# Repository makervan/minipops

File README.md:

# MiniPops
PCB design for Jan Ostman's O2 synth. Based around the Arduino Pro Mini board.

## License
Hardware designs created by Severin Schols, and shared under CC-BY-SA-4.0. See LICENSE for more information.

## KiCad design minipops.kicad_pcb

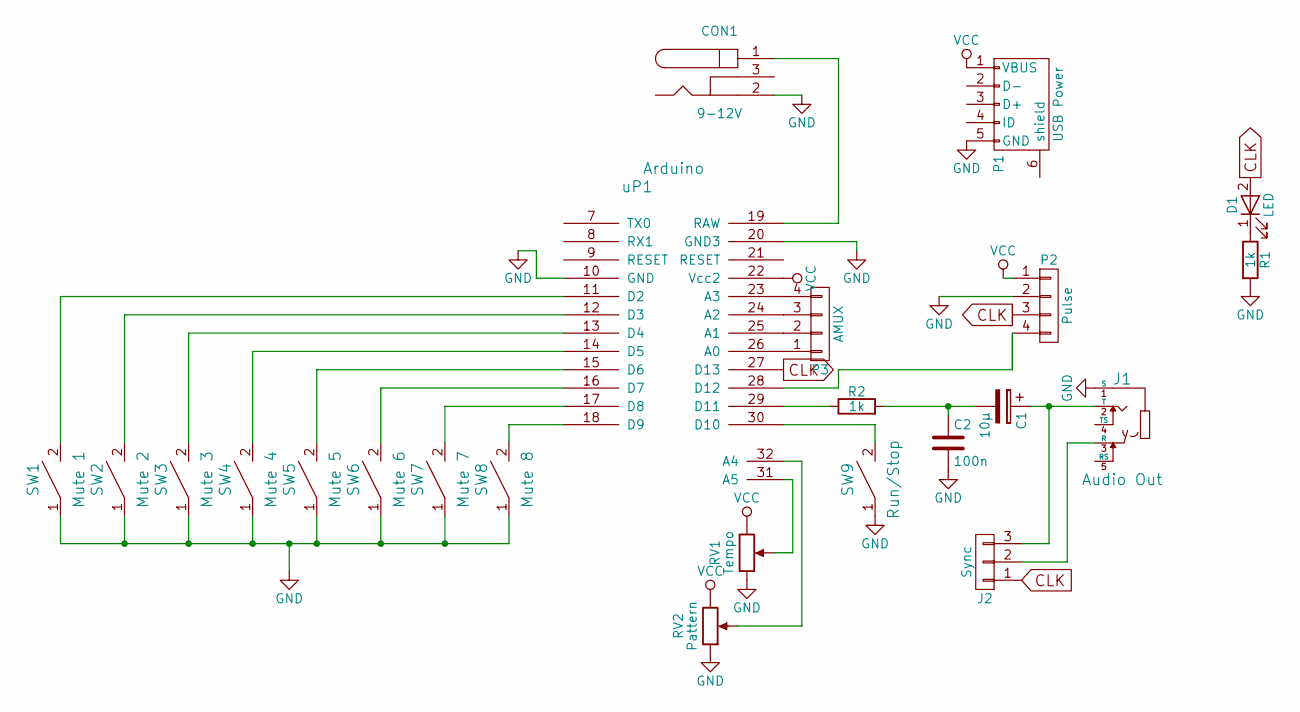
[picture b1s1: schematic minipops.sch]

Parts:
C1: 10µ; C_Radial_D5_L6_P2.5
C2: 100n; C_Rect_L4_W2.5_P2.5
CON1: 9-12V; BARREL_JACK
D1: LED; LED-5MM
J1: Audio Out; AudioJack3.5mm
J2: Sync; Pin_Header_Straight_1x03
P1: USB Power; USB_Micro-B
P2: Pulse; Pin_Header_Straight_1x04
P3: AMUX; Pin_Header_Straight_1x04
R1, R2: 1k; Resistor_Horizontal_RM10mm
RV1: Tempo; Potentiometer_Alpha-RV09
RV2: Pattern; Potentiometer_Alpha-RV09
SW1: Mute 1; Pin_Header_Straight_1x03
SW2: Mute 2; Pin_Header_Straight_1x03
SW3: Mute 3; Pin_Header_Straight_1x03
SW4: Mute 4; Pin_Header_Straight_1x03
SW5: Mute 5; Pin_Header_Straight_1x03
SW6: Mute 6; Pin_Header_Straight_1x03
SW7: Mute 7; Pin_Header_Straight_1x03
SW8: Mute 8; Pin_Header_Straight_1x03
SW9: Run/Stop; Pin_Header_Straight_1x03
uP1: Arduino; ArduProMini-6

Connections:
CLK: D1.2 (A), J2.1, P2.3, uP1.27 (D13)
GND: C2.2, CON1.2, J1.1 (S), P1.5 (GND), P2.2, R1.2, RV1.1, RV2.1, SW1.1, SW2.1, SW3.1, SW4.1, SW5.1, SW6.1, SW7.1, SW8.1, SW9.1, uP1.10 (GND), uP1.20 (GND3)
unnamed: C1.1, J1.2 (T), J2.3
unnamed: C1.2, C2.1, R2.2
unnamed: CON1.1, uP1.19 (RAW)
unnamed: D1.1 (K), R1.1
unnamed: J1.3 (R), J2.2
unnamed: P2.4, uP1.28 (D12)
unnamed: P3.1, uP1.26 (A0)
unnamed: P3.2, uP1.25 (A1)
unnamed: P3.3, uP1.24 (A2)
unnamed: P3.4, uP1.23 (A3)
unnamed: R2.1, uP1.29 (D11)
unnamed: RV1.2, uP1.31 (A5)
unnamed: RV2.2, uP1.32 (A4)
unnamed: SW1.2, uP1.11 (D2)
unnamed: SW2.2, uP1.12 (D3)
unnamed: SW3.2, uP1.13 (D4)
unnamed: SW4.2, uP1.14 (D5)
unnamed: SW5.2, uP1.15 (D6)
unnamed: SW6.2, uP1.16 (D7)
unnamed: SW7.2, uP1.17 (D8)
unnamed: SW8.2, uP1.18 (D9)
unnamed: SW9.2, uP1.30 (D10)
VCC: P1.1 (VBUS), P2.1, RV1.3, RV2.3, uP1.22 (Vcc2)

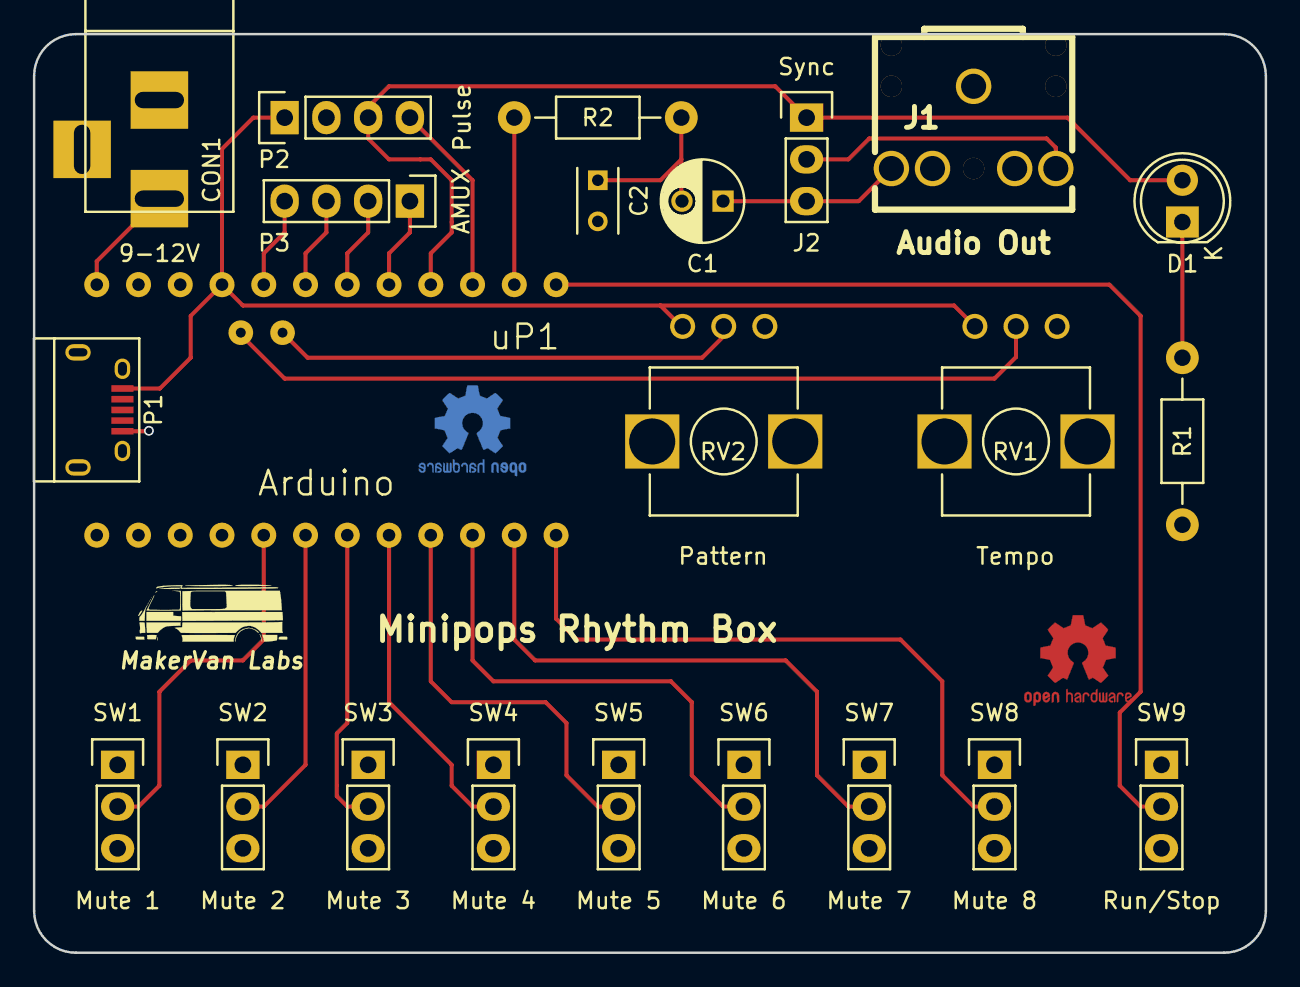
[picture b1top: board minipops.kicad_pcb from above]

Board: 2 copper layers, 74.9 x 55.9 mm, 23 parts (0 on the bottom side), 25 nets.

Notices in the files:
minipops.kicad_pcb:
Licensed under CC BY-SA 4.0
